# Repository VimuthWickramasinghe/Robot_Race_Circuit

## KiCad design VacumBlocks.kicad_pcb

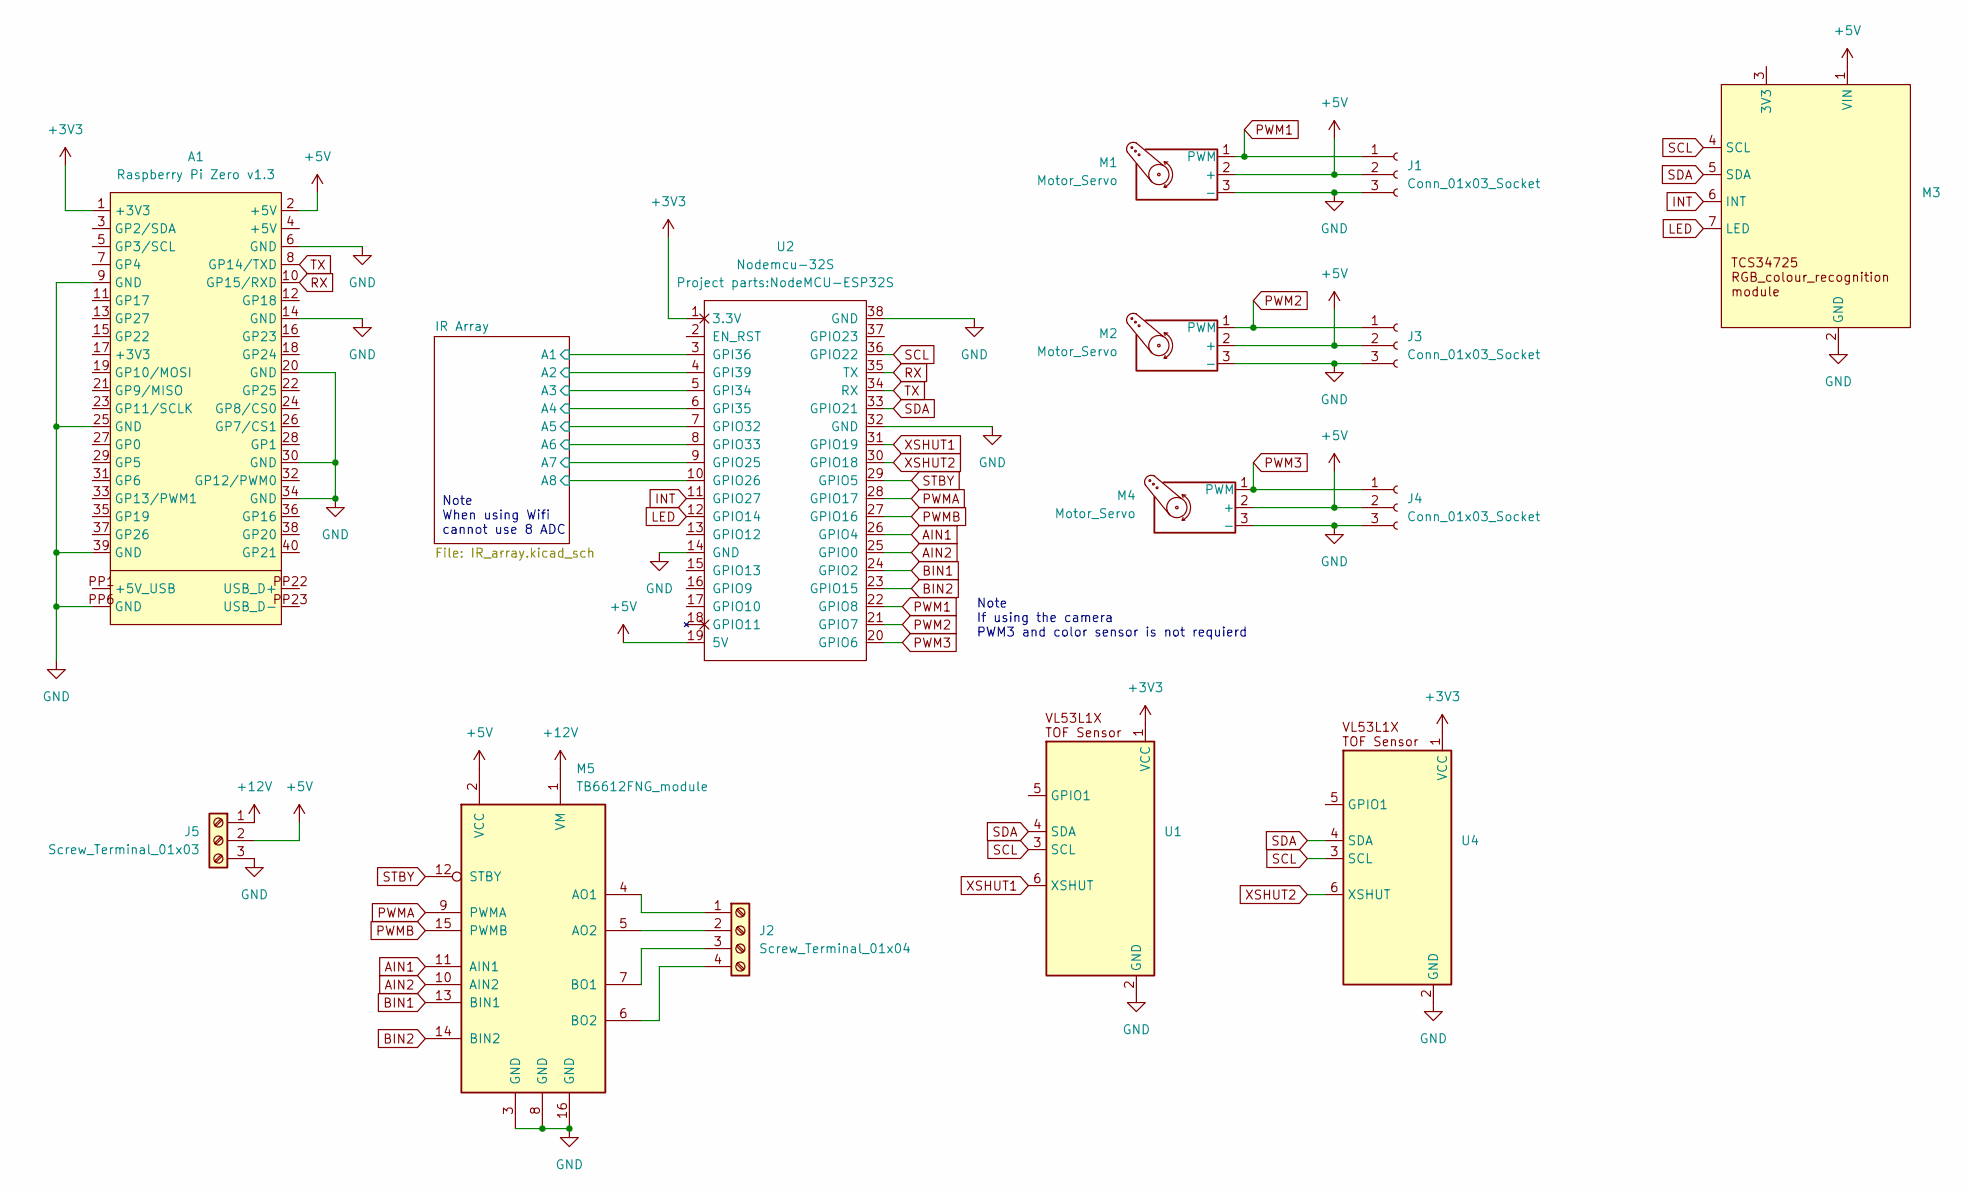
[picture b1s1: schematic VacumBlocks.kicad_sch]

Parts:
A1: Raspberry Pi Zero v1.3; RASPI_ZERO_FULL
J1, J3, J4: Conn_01x03_Socket; PinHeader_1x03_P2.54mm_Vertical
J2: Screw_Terminal_01x04; TerminalBlock_MaiXu_MX126-5.0-04P_1x04_P5.00mm
J5: Screw_Terminal_01x03; TerminalBlock_MaiXu_MX126-5.0-03P_1x03_P5.00mm
M1, M2, M4: Motor_Servo
M3: TCS34725_RGB_module
M5: TB6612FNG_module
U1, U4: VL53L0XV2 TOF Sensor moule
U2: Nodemcu-32S; NodeMCU-ESP32S

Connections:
+3V3: A1.1 (+3V3), U1.1 (VCC), U2.1 (3.3V), U4.1 (VCC); also elsewhere on the board
+5V: A1.2 (+5V), J1.2, J3.2, J4.2, J5.2, M1.2 (+), M2.2 (+), M3.1 (VIN), M4.2 (+), M5.2 (VCC), U2.19 (5V)
+12V: J5.1, M5.1 (VM)
/IR Array/A1: U2.3 (GPI36); also elsewhere on the board
/IR Array/A2: U2.4 (GPI39); also elsewhere on the board
/IR Array/A3: U2.5 (GPI34); also elsewhere on the board
/IR Array/A4: U2.6 (GPI35); also elsewhere on the board
/IR Array/A5: U2.7 (GPIO32); also elsewhere on the board
/IR Array/A6: U2.8 (GPIO33); also elsewhere on the board
/IR Array/A7: U2.9 (GPIO25); also elsewhere on the board
/IR Array/A8: U2.10 (GPIO26); also elsewhere on the board
AIN1: M5.11 (AIN1), U2.26 (GPIO4)
AIN2: M5.10 (AIN2), U2.25 (GPIO0)
BIN1: M5.13 (BIN1), U2.24 (GPIO2)
BIN2: M5.14 (BIN2), U2.23 (GPIO15)
GND: A1.6 (GND), A1.9 (GND), A1.14 (GND), A1.20 (GND), A1.25 (GND), A1.30 (GND), A1.34 (GND), A1.39 (GND), A1.PP6 (GND), J1.3, J3.3, J4.3, J5.3, M1.3 (-), M2.3 (-), M3.2 (GND), M4.3 (-), M5.3 (GND), M5.8 (GND), M5.16 (GND), U1.2 (GND), U2.14 (GND), U2.32 (GND), U2.38 (GND), U4.2 (GND); also elsewhere on the board
INT: M3.6 (INT), U2.11 (GPIO27)
LED: M3.7 (LED), U2.12 (GPIO14)
unnamed: J2.1, M5.4 (AO1)
unnamed: J2.2, M5.5 (AO2)
unnamed: J2.3, M5.7 (BO1)
unnamed: J2.4, M5.6 (BO2)
PWM1: J1.1, M1.1 (PWM), U2.22 (GPIO8)
PWM2: J3.1, M2.1 (PWM), U2.21 (GPIO7)
PWM3: J4.1, M4.1 (PWM), U2.20 (GPIO6)
PWMA: M5.9 (PWMA), U2.28 (GPIO17)
PWMB: M5.15 (PWMB), U2.27 (GPIO16)
RX: A1.10 (GP15/RXD), U2.35 (TX)
SCL: M3.4 (SCL), U1.3 (SCL), U2.36 (GPIO22), U4.3 (SCL)
SDA: M3.5 (SDA), U1.4 (SDA), U2.33 (GPIO21), U4.4 (SDA)
STBY: M5.12 (STBY), U2.29 (GPIO5)
TX: A1.8 (GP14/TXD), U2.34 (RX)
XSHUT1: U1.6 (XSHUT), U2.31 (GPIO19)
XSHUT2: U2.30 (GPIO18), U4.6 (XSHUT)

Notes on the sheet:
Note If using the camera PWM3 and color sensor is not requierd
Note When using Wifi cannot use 8 ADC

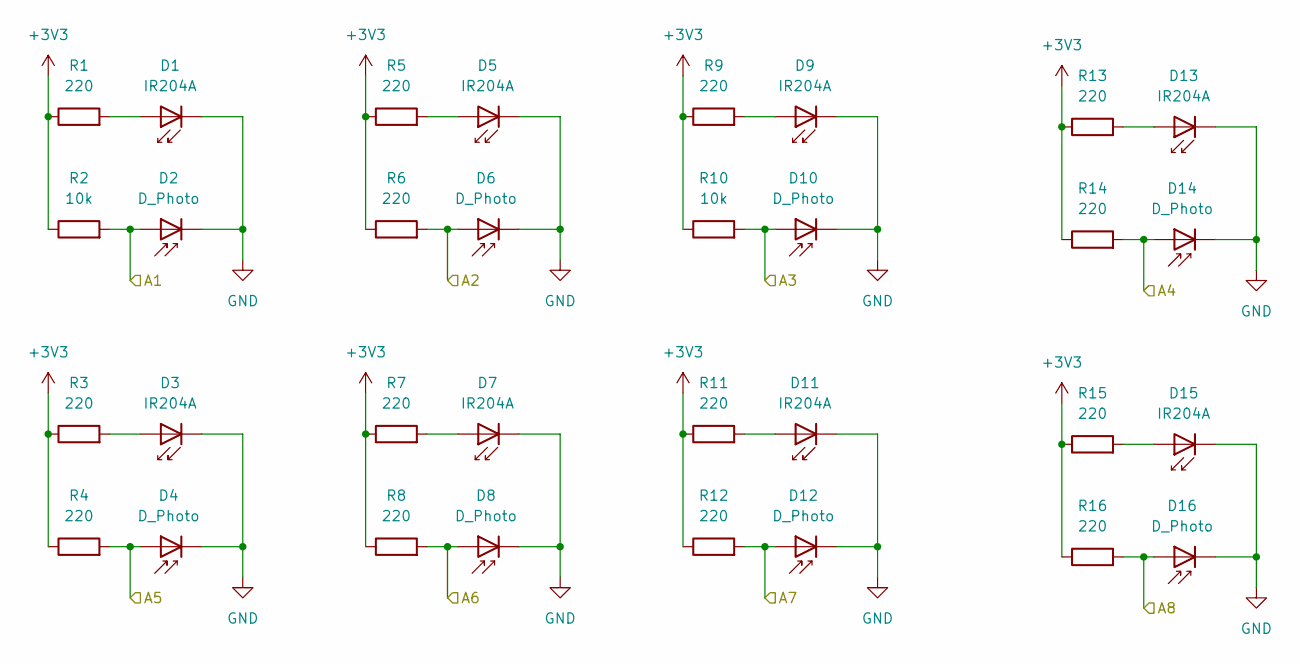
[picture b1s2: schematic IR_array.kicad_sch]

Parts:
D1, D3, D5, D7, D9, D11, D13, D15: IR204A; LED_D5.0mm
D2, D4, D6, D8, D10, D12, D14, D16: D_Photo; LED_D5.0mm_IRBlack
R1, R3, R4, R5, R6, R7, R8, R9, R11, R12, R13, R14, R15, R16: 220; R_Axial_DIN0204_L3.6mm_D1.6mm_P5.08mm_Horizontal
R2, R10: 10k; R_Axial_DIN0204_L3.6mm_D1.6mm_P5.08mm_Horizontal

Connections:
+3V3: R1.1, R2.1, R3.1, R4.1, R5.1, R6.1, R7.1, R8.1, R9.1, R10.1, R11.1, R12.1, R13.1, R14.1, R15.1, R16.1; also elsewhere on the board
/IR Array/A1: D2.2 (A), R2.2; also elsewhere on the board
/IR Array/A2: D6.2 (A), R6.2; also elsewhere on the board
/IR Array/A3: D10.2 (A), R10.2; also elsewhere on the board
/IR Array/A4: D14.2 (A), R14.2; also elsewhere on the board
/IR Array/A5: D4.2 (A), R4.2; also elsewhere on the board
/IR Array/A6: D8.2 (A), R8.2; also elsewhere on the board
/IR Array/A7: D12.2 (A), R12.2; also elsewhere on the board
/IR Array/A8: D16.2 (A), R16.2; also elsewhere on the board
GND: D1.1 (K), D2.1 (K), D3.1 (K), D4.1 (K), D5.1 (K), D6.1 (K), D7.1 (K), D8.1 (K), D9.1 (K), D10.1 (K), D11.1 (K), D12.1 (K), D13.1 (K), D14.1 (K), D15.1 (K), D16.1 (K); also elsewhere on the board
unnamed: D1.2 (A), R1.2
unnamed: D3.2 (A), R3.2
unnamed: D5.2 (A), R5.2
unnamed: D7.2 (A), R7.2
unnamed: D9.2 (A), R9.2
unnamed: D11.2 (A), R11.2
unnamed: D13.2 (A), R13.2
unnamed: D15.2 (A), R15.2

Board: 2 copper layers, 43 parts (0 on the bottom side), 42 nets, no tracks yet.
